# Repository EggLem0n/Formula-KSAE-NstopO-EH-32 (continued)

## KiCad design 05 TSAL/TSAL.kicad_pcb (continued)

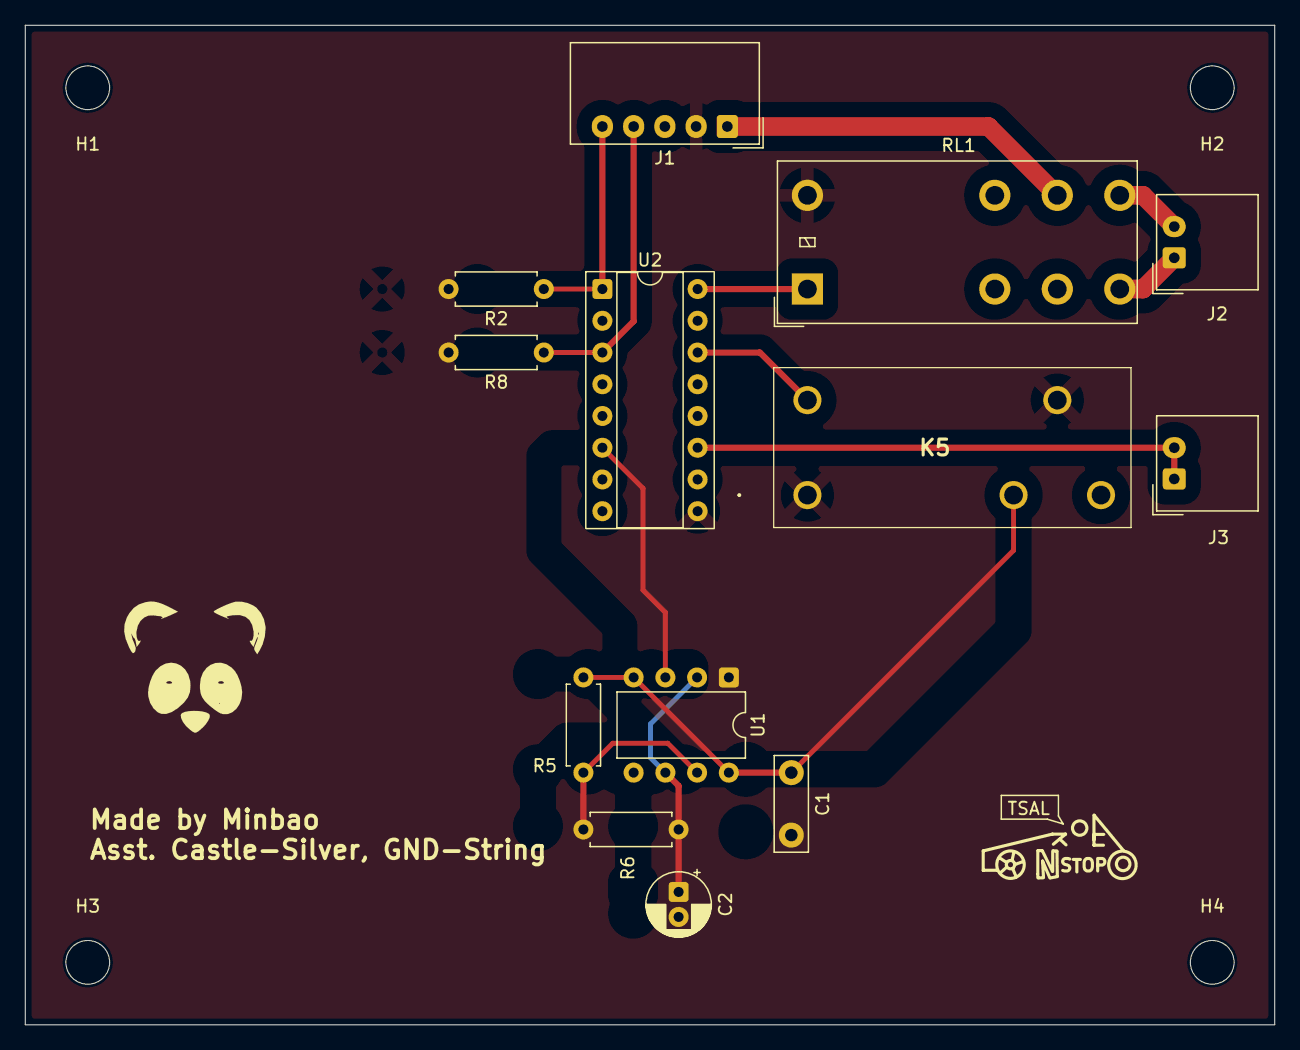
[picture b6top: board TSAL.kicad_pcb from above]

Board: 2 copper layers, 100.0 x 80.0 mm, 17 parts (0 on the bottom side), 14 nets.

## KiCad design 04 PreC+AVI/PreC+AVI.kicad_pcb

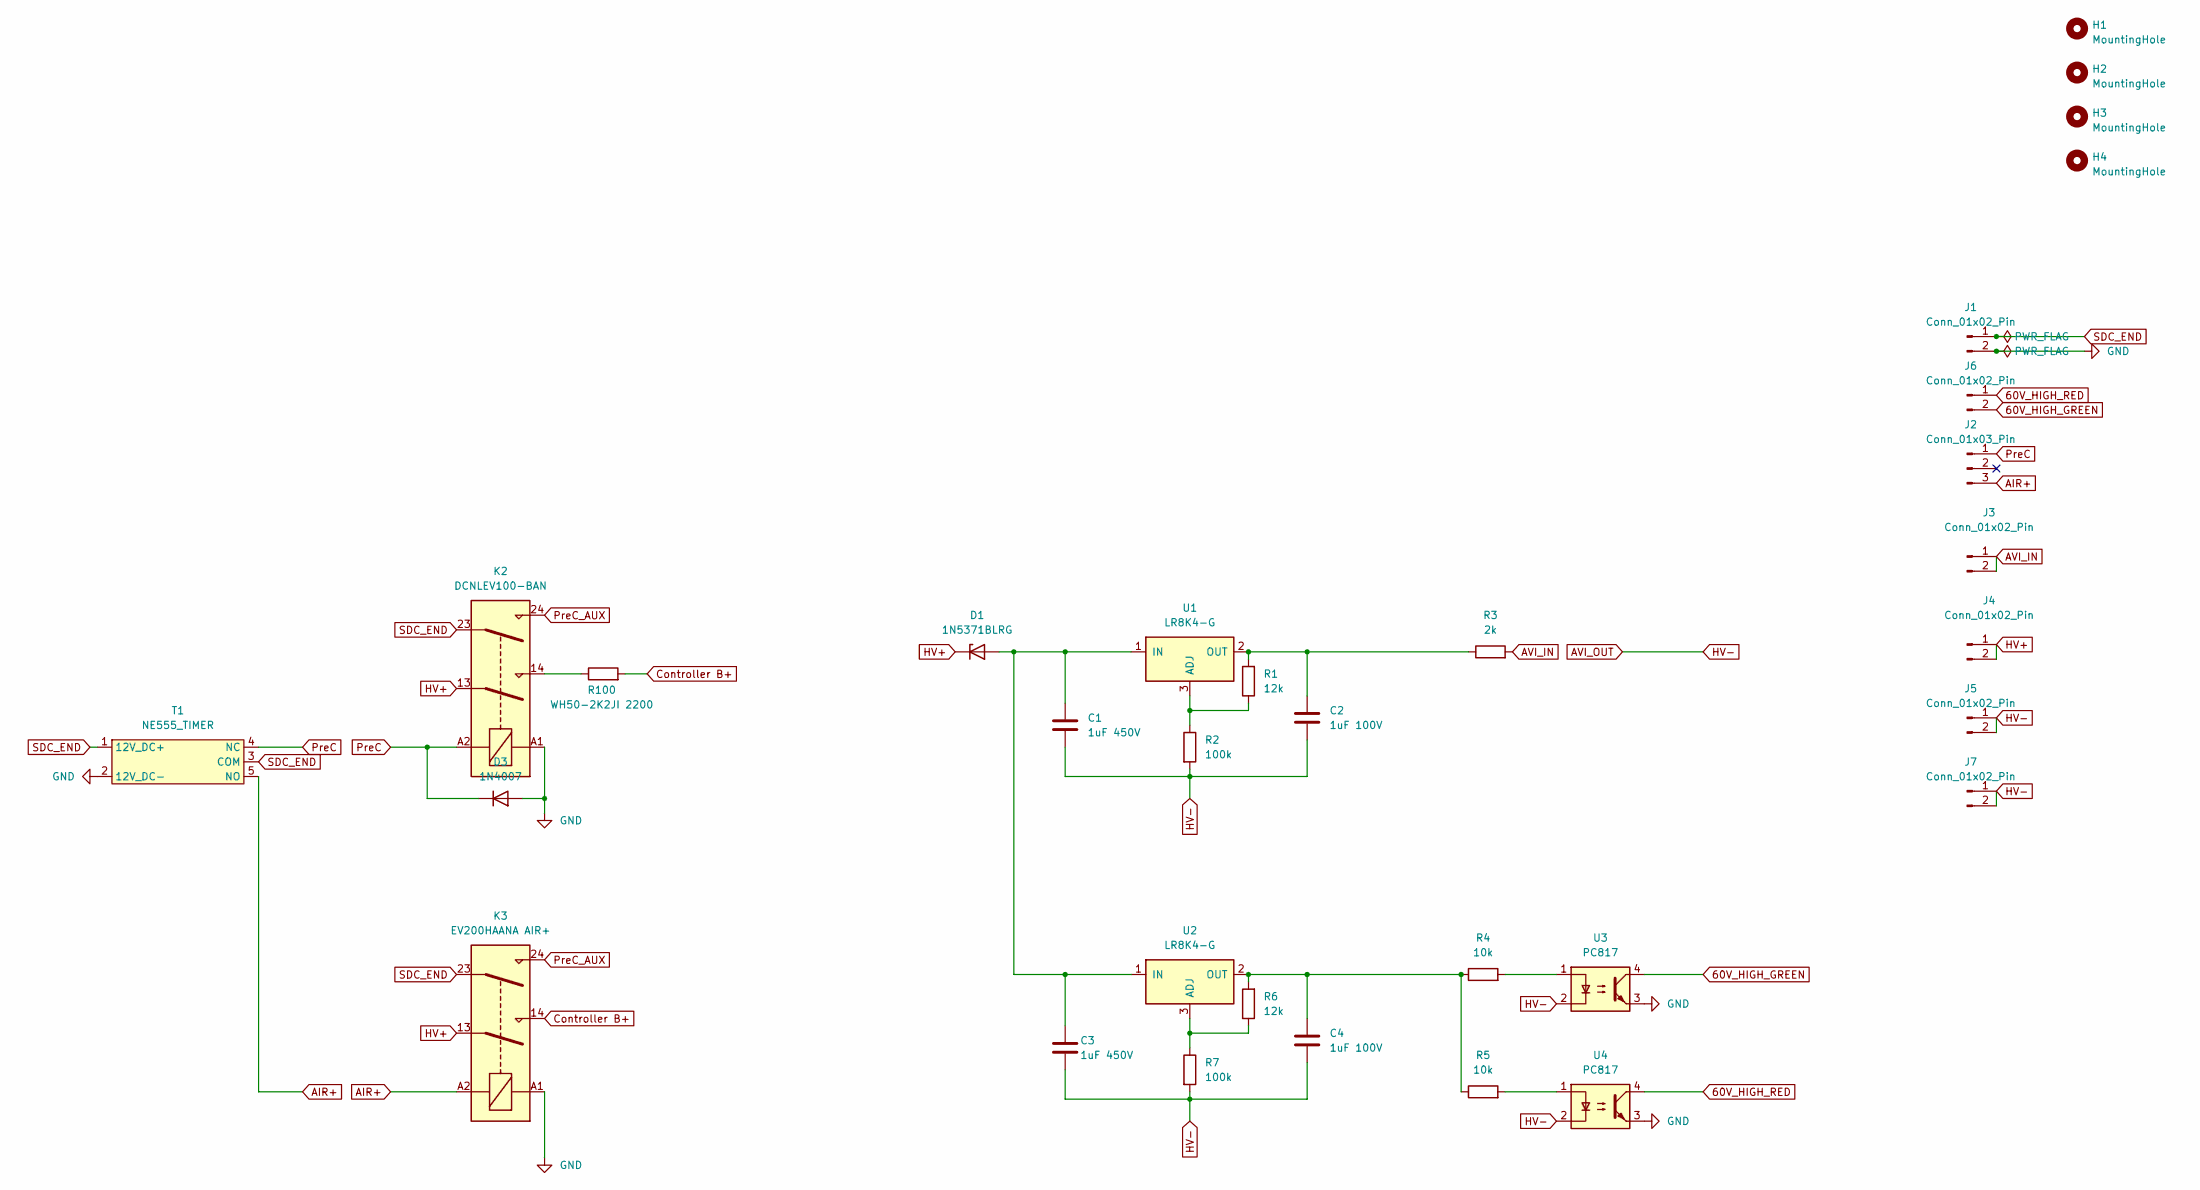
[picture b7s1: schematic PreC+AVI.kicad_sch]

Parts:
C1, C3: 1uF 450V; C_Rect_L18.0mm_W7.0mm_P15.00mm_FKS3_FKP3
C2, C4: 1uF 100V; C_Disc_D7.5mm_W5.0mm_P5.00mm
D1: 1N5371BLRG; D_DO-201_P15.24mm_Horizontal
D3: 1N4007; D_DO-41_SOD81_P10.16mm_Horizontal
H1, H2, H3, H4: MountingHole; MountingHole_3.5mm
J1, J6: Conn_01x02_Pin; Molex_SPOX_5267-02A_1x02_P2.50mm_Vertical
J2: Conn_01x03_Pin; Molex_SPOX_5267-03A_1x03_P2.50mm_Vertical
J3, J4, J5, J7: Conn_01x02_Pin; AMASS_XT30U-M_1x02_P5.0mm_Vertical
K2: DCNLEV100-BAN
K3: EV200HAANA AIR+
R1, R6: 12k; R_Axial_DIN0207_L6.3mm_D2.5mm_P7.62mm_Horizontal
R2, R7: 100k; R_Axial_DIN0207_L6.3mm_D2.5mm_P7.62mm_Horizontal
R3: 2k; R_Axial_DIN0207_L6.3mm_D2.5mm_P7.62mm_Horizontal
R4, R5: 10k; R_Axial_DIN0207_L6.3mm_D2.5mm_P7.62mm_Horizontal
R100: WH50-2K2JI 2200
T1: NE555_TIMER; HAM1227_molex5267_conn_fine
U1, U2: LR8K4-G; TO-252-2
U3, U4: PC817; DIP-4_W7.62mm

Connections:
60V_HIGH_GREEN: J6.2, U3.4
60V_HIGH_RED: J6.1, U4.4
AIR+: J2.3, K3.A2, T1.5 (NO)
AVI_IN: J3.1, J3.2, R3.2
AVI_OUT: C1.2, C2.2, C3.2, C4.2, J5.1, J5.2, J7.1, J7.2, R2.2, R7.2, U3.2, U4.2
GND: D3.2 (A), J1.2, K2.A1, K3.A1, T1.2 (12V_DC-), U3.3, U4.3
HV+: D1.1 (K), J4.1, J4.2, K2.13, K3.13
unnamed: C1.1, C3.1, D1.2 (A), U1.1 (IN), U2.1 (IN)
unnamed: K2.14, R100.1
unnamed: K2.24, K3.24
unnamed: K3.14, R100.2
unnamed: R4.2, U3.1
unnamed: R5.2, U4.1
unnamed: R1.1, R2.1, U1.3 (ADJ)
unnamed: C2.1, R1.2, R3.1, U1.2 (OUT)
unnamed: R6.1, R7.1, U2.3 (ADJ)
unnamed: C4.1, R4.1, R5.1, R6.2, U2.2 (OUT)
PreC: D3.1 (K), J2.1, K2.A2, T1.4 (NC)
SDC_END: J1.1, K2.23, K3.23, T1.1 (12V_DC+), T1.3 (COM)

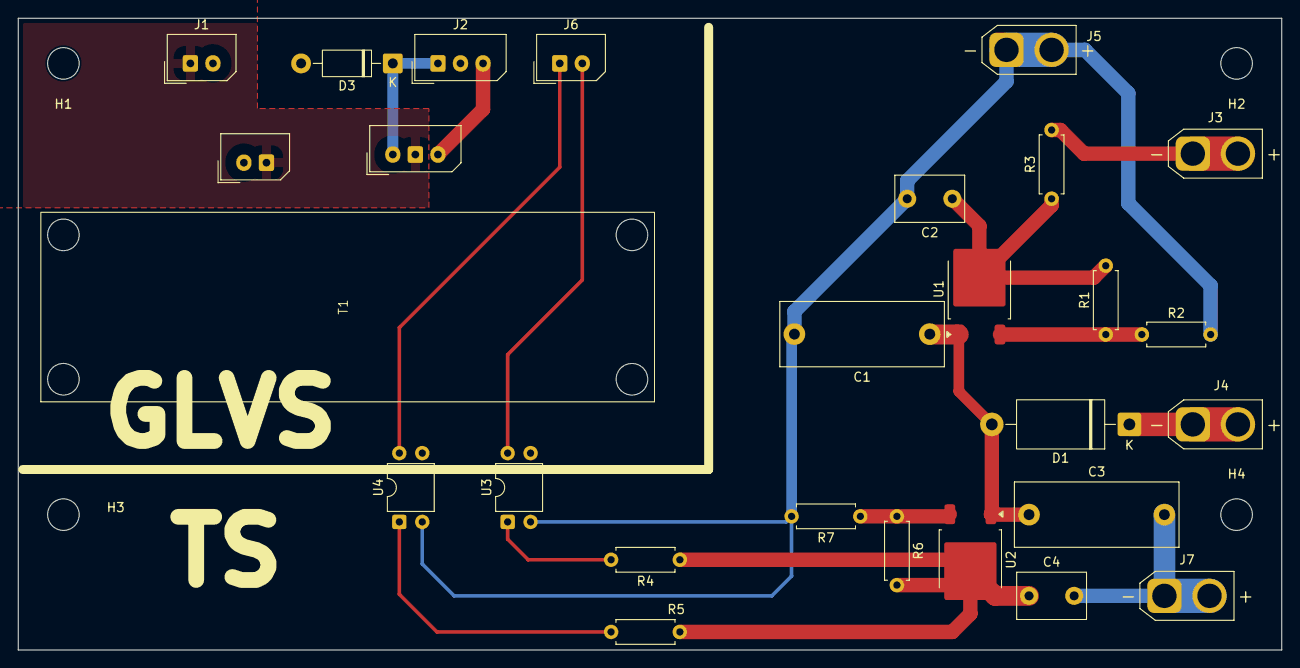
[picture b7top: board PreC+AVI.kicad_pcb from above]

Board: 2 copper layers, 140.0 x 70.0 mm, 29 parts (0 on the bottom side), 16 nets.

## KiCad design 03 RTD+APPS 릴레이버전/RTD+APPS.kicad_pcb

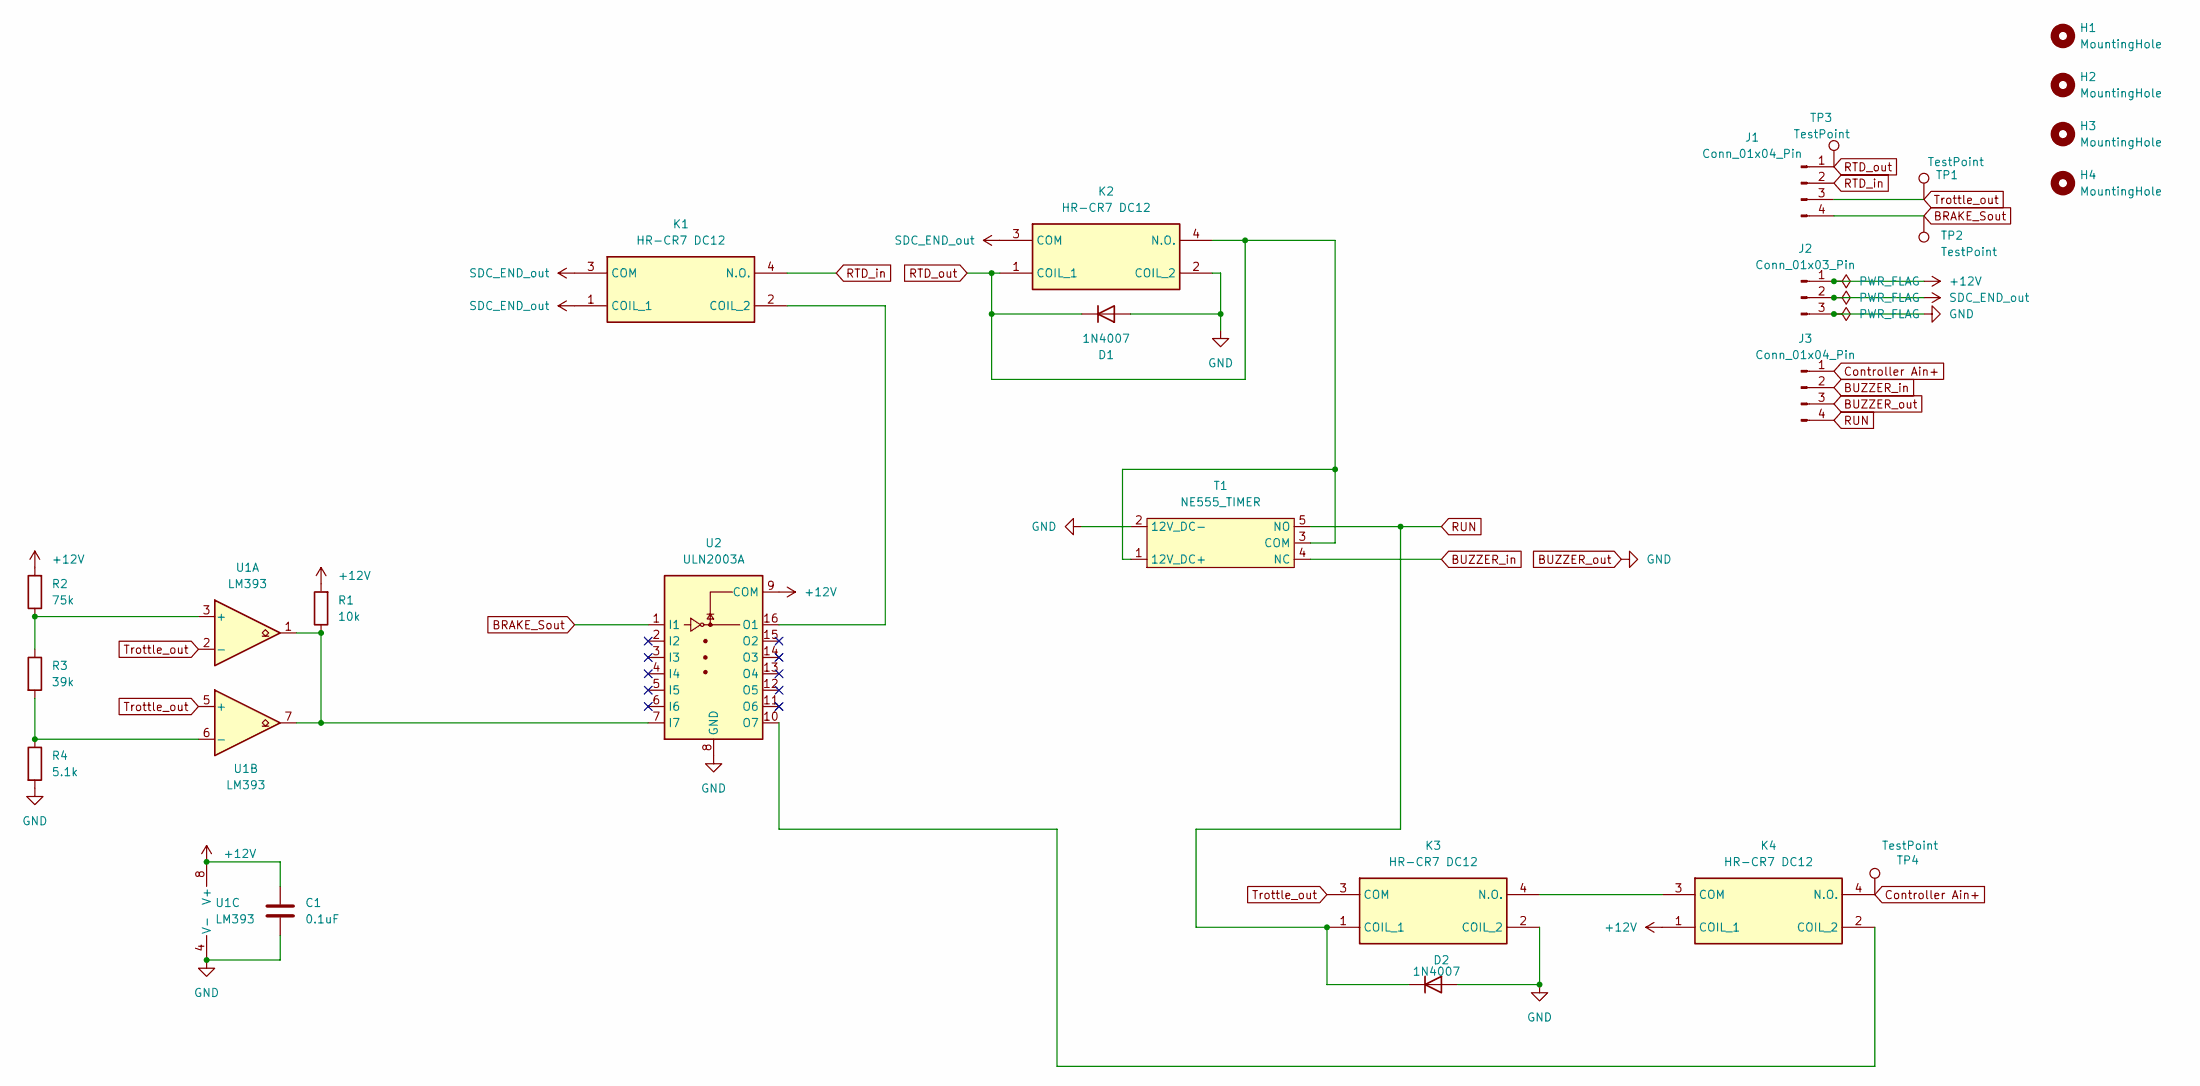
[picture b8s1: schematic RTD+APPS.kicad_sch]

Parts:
C1: 0.1uF; C_Disc_D7.5mm_W2.5mm_P5.00mm
D1, D2: 1N4007; D_DO-41_SOD81_P10.16mm_Horizontal
H1, H2, H3, H4: MountingHole; MountingHole_3.5mm
J1, J3: Conn_01x04_Pin; Molex_SPOX_5268-04A_1x04_P2.50mm_Horizontal
J2: Conn_01x03_Pin; Molex_SPOX_5268-03A_1x03_P2.50mm_Horizontal
K1, K2, K3, K4: HR-CR7 DC12; Manufacturer_Part_Number JW1FSN-DC12V; Mouser Part Number 769-JW1FSN-DC12V
R1: 10k; R_Axial_DIN0207_L6.3mm_D2.5mm_P7.62mm_Horizontal
R2: 75k; R_Axial_DIN0207_L6.3mm_D2.5mm_P7.62mm_Horizontal
R3: 39k; R_Axial_DIN0207_L6.3mm_D2.5mm_P7.62mm_Horizontal
R4: 5.1k; R_Axial_DIN0207_L6.3mm_D2.5mm_P7.62mm_Horizontal
T1: NE555_TIMER; HAM1227_molex5267_conn_fine
TP1, TP2, TP3, TP4: TestPoint; TestPoint_Keystone_5000-5004_Miniature
U1: LM393; DIP-8_W7.62mm
U2: ULN2003A; DIP-16_W7.62mm

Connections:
+12V: C1.2, J2.1, K4.1 (COIL_1), R1.2, R2.2, U1.8 (V+), U2.9 (COM)
BRAKE_Sout: J1.4, TP2.1, U2.1 (I1)
BUZZER_in: J3.2, T1.4 (NC)
BUZZER_out: C1.1, D1.2 (A), D2.2 (A), J2.3, J3.3, K2.2 (COIL_2), K3.2 (COIL_2), R4.2, T1.2 (12V_DC-), U1.4 (V-), U2.8 (GND)
Controller Ain+: J3.1, K4.4 (N.O.), TP4.1
unnamed: K1.2 (COIL_2), U2.16 (O1)
unnamed: K3.4 (N.O.), K4.3 (COM)
unnamed: K4.2 (COIL_2), U2.10 (O7)
unnamed: R2.1, R3.1, U1.3 (+)
unnamed: R3.2, R4.1, U1.6 (-)
unnamed: R1.1, U1.1, U1.7, U2.7 (I7)
RTD_in: J1.2, K1.4 (N.O.)
RTD_out: D1.1 (K), J1.1, K2.1 (COIL_1), K2.4 (N.O.), T1.1 (12V_DC+), T1.3 (COM), TP3.1
RUN: D2.1 (K), J3.4, K3.1 (COIL_1), T1.5 (NO)
SDC_END_out: J2.2, K1.1 (COIL_1), K1.3 (COM), K2.3 (COM)
Trottle_out: J1.3, K3.3 (COM), TP1.1, U1.2 (-), U1.5 (+)

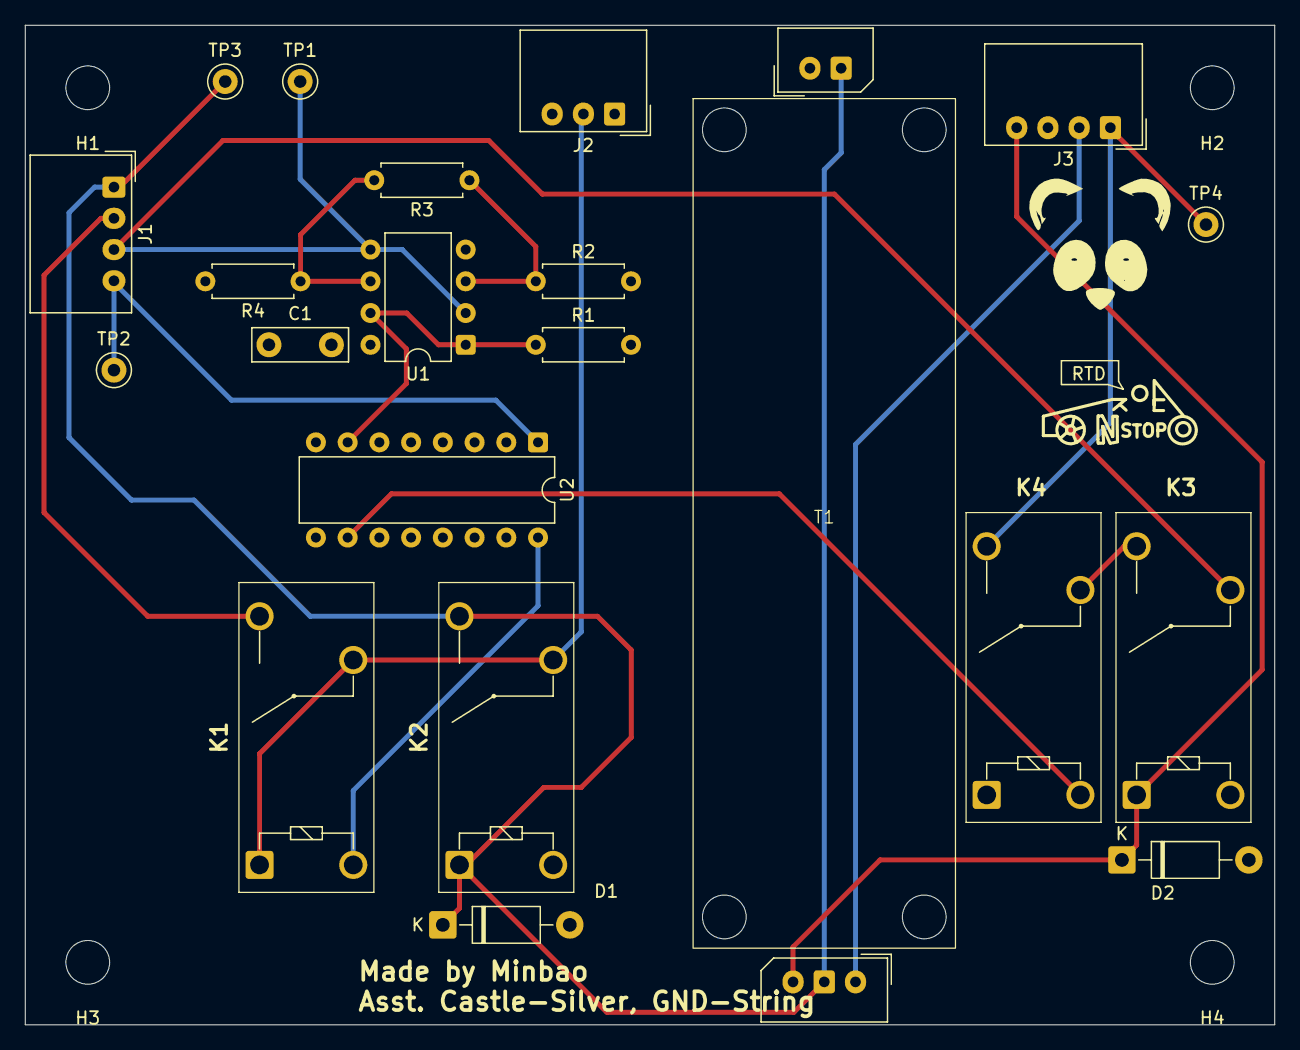
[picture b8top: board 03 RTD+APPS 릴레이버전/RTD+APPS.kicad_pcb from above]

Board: 4 copper layers, 100.0 x 80.0 mm, 25 parts (0 on the bottom side), 16 nets.
